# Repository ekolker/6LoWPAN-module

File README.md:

**[UNMAINTAINED] This library does not have a maintainer. The source code and repository will be kept at this URL indefinitely. If you'd like to help maintain this codebase, create an issue on this repo explaining why you'd like to become a maintainer and tag @tessel/maintainers in the body.**

6LoWPAN-module
==============

A [6LoWPAN](http://en.wikipedia.org/wiki/6LoWPAN) module for Tessel.

Designs in KiCad.

### License

Copyright 2014 Technical Machine, Inc.

CC-BY-SA

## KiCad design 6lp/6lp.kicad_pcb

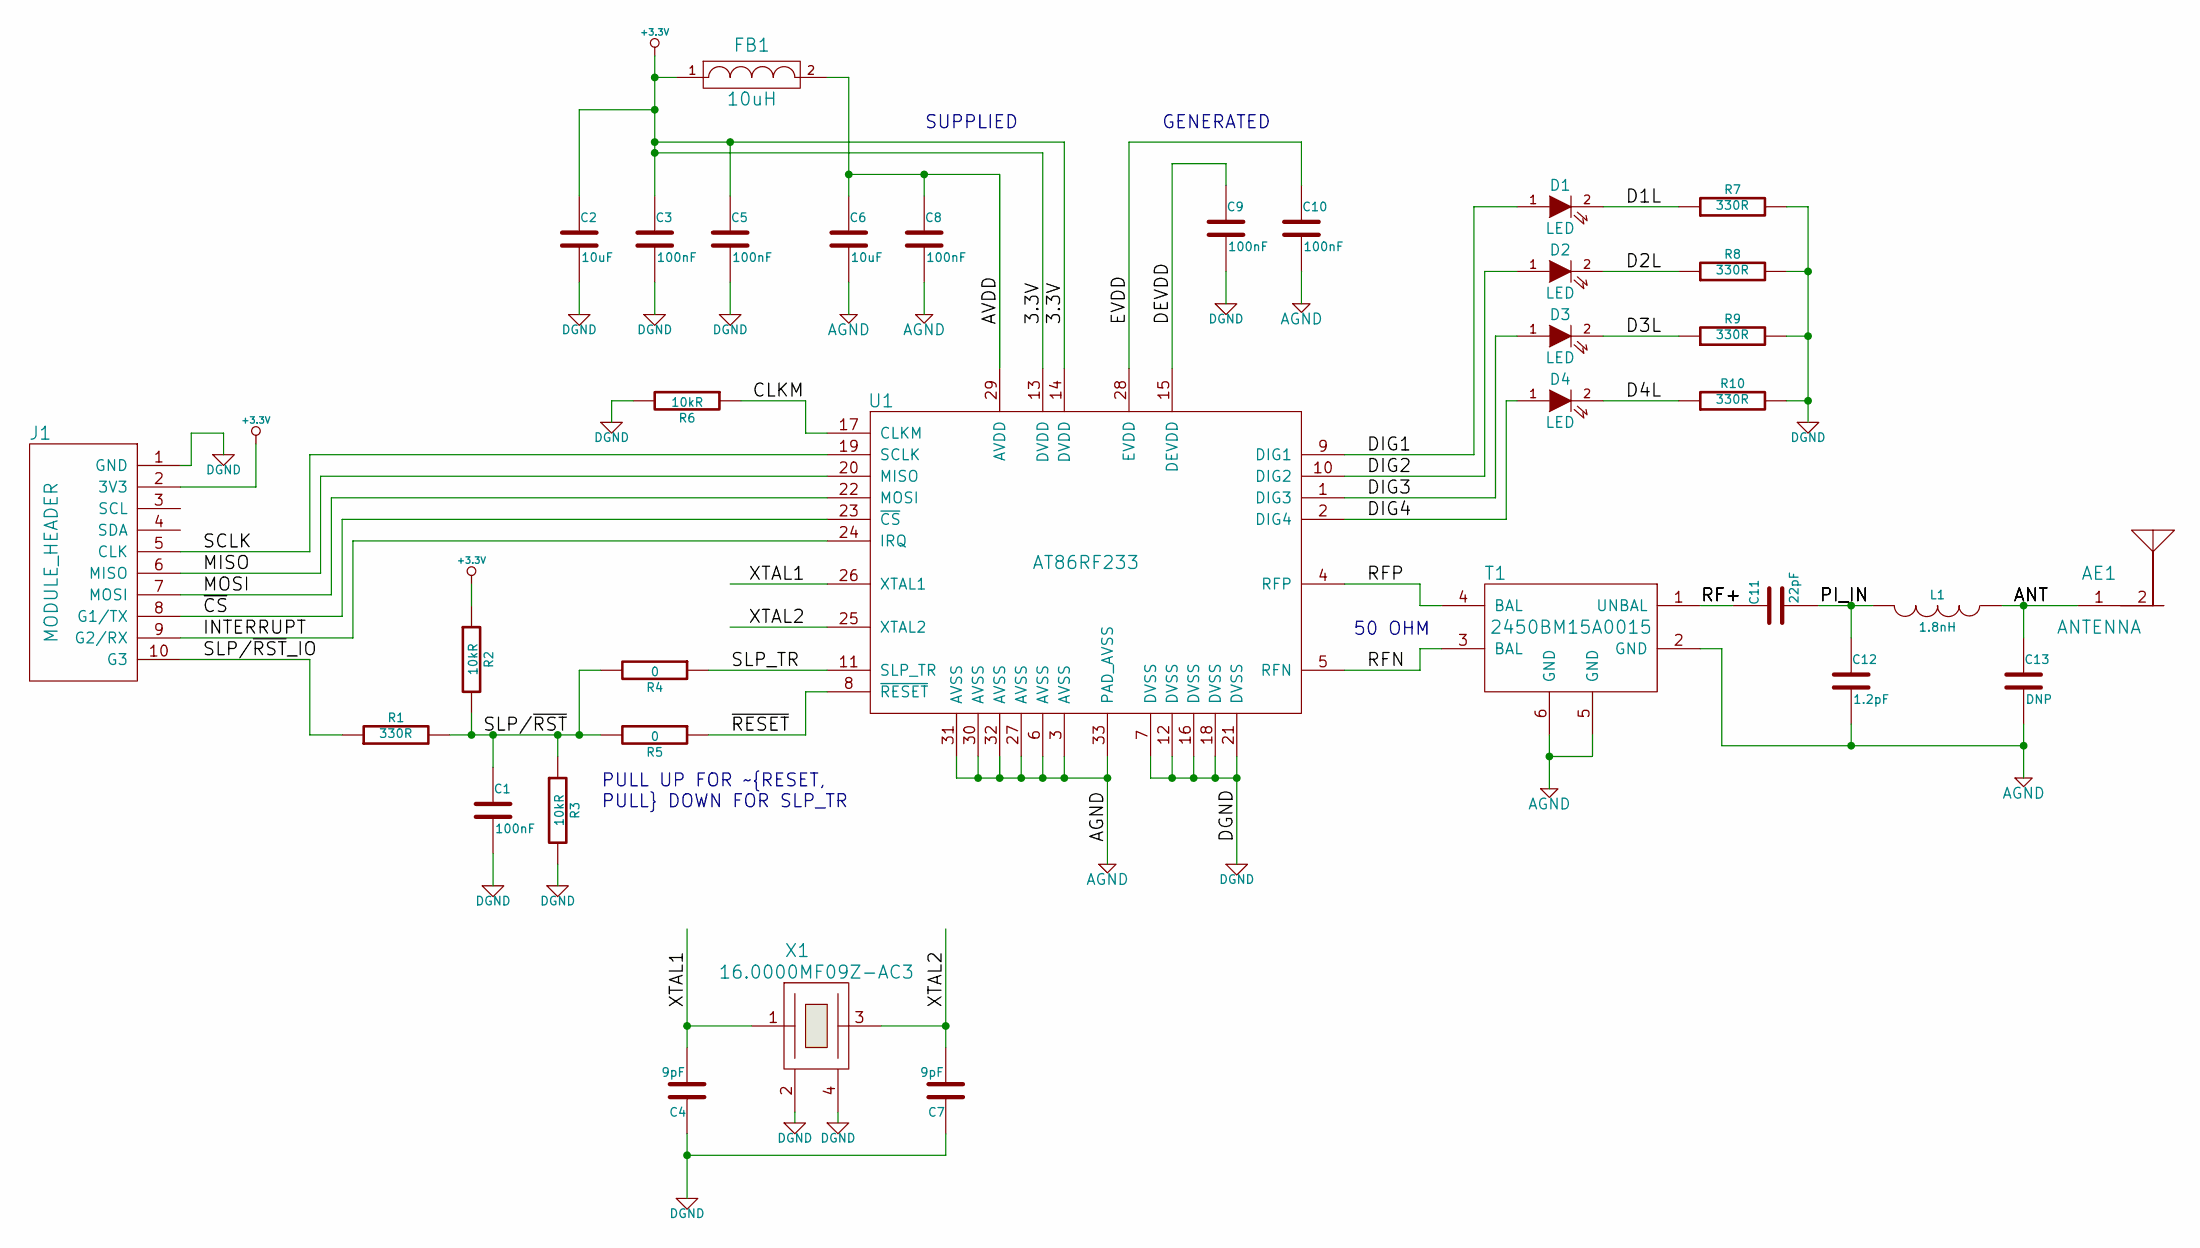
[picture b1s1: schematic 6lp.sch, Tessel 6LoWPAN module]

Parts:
AE1: ANTENNA; ANTENNA-SMT-2.45GHz
C1, C3, C5, C8, C9, C10: 100nF; C_0402
C2, C6: 10uF; C_0805
C4, C7: 9pF; C_0402
C11: 22pF; C_0402
C12: 1.2pF; C_0402
C13: DNP; C_0402
D1, D2, D3, D4: LED; LED-0603
FB1: 10uH; C_0603
J1: MODULE_HEADER; MODULE_HEADER_MODULE
L1: 1.8nH; C_0402
R1, R7, R8, R9, R10: 330R; R_0402
R2, R3, R6: 10kR; R_0402
R4, R5: 0; R_0402
T1: 2450BM15A0015
U1: AT86RF233; QFN-32-1EP
X1: 16.0000MF09Z-AC3; TSX-3225

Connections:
+3.3V: C2.1, C3.1, C5.1, FB1.1, J1.2 (3V3), R2.1, U1.13 (DVDD), U1.14 (DVDD)
/ANT: AE1.1, C13.1, L1.1
/AVDD: C6.1, C8.1, FB1.2, U1.29 (AVDD)
/CLKM: R6.1, U1.17 (CLKM)
/D1L: D1.2 (K), R7.1
/D2L: D2.2 (K), R8.1
/D3L: D3.2 (K), R9.1
/D4L: D4.2 (K), R10.1
/DEVDD: C9.1, U1.15 (DEVDD)
/DIG1: D1.1 (A), U1.9 (DIG1)
/DIG2: D2.1 (A), U1.10 (DIG2)
/DIG3: D3.1 (A), U1.1 (DIG3)
/DIG4: D4.1 (A), U1.2 (DIG4)
/EVDD: C10.1, U1.28 (EVDD)
/INTERRUPT: J1.9 (G2/RX), U1.24 (IRQ)
/MISO: J1.6 (MISO), U1.20 (MISO)
/MOSI: J1.7 (MOSI), U1.22 (MOSI)
/PI_IN: C11.2, C12.1, L1.2
/RF+: C11.1, T1.1 (UNBAL)
/RFN: T1.3 (BAL), U1.5 (RFN)
/RFP: T1.4 (BAL), U1.4 (RFP)
/SCLK: J1.5 (CLK), U1.19 (SCLK)
/SLP/~RST: C1.1, R1.2, R2.2, R3.1, R4.2, R5.2
/SLP/~RST~_IO: J1.10 (G3), R1.1
/SLP_TR: R4.1, U1.11 (SLP_TR)
/XTAL1: C4.2, U1.26 (XTAL1), X1.1
/XTAL2: C7.2, U1.25 (XTAL2), X1.3
/~CS: J1.8 (G1/TX), U1.23 (~CS)
/~RESET: R5.1, U1.8 (~RESET)
AGND: C6.2, C8.2, C10.2, C12.2, C13.2, T1.2 (GND), T1.5 (GND), T1.6 (GND), U1.3 (AVSS), U1.6 (AVSS), U1.27 (AVSS), U1.30 (AVSS), U1.31 (AVSS), U1.32 (AVSS), U1.33 (PAD_AVSS); also elsewhere on the board
DGND: C1.2, C2.2, C3.2, C4.1, C5.2, C7.1, C9.2, J1.1 (GND), R3.2, R6.2, R7.2, R8.2, R9.2, R10.2, U1.7 (DVSS), U1.12 (DVSS), U1.16 (DVSS), U1.18 (DVSS), U1.21 (DVSS), X1.2, X1.4; also elsewhere on the board

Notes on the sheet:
GENERATED
SUPPLIED
50 OHM
PULL UP FOR ~RESET, PULL DOWN FOR SLP_TR

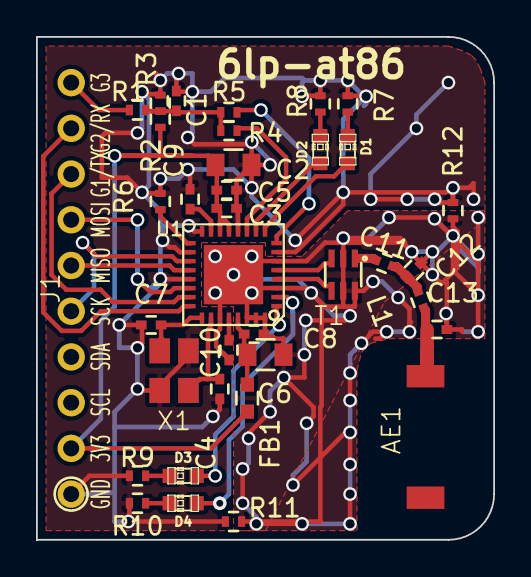
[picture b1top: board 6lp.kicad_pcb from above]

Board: 2 copper layers, 25.4 x 27.9 mm, 36 parts (0 on the bottom side), 31 nets.

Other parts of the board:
R11, R12: 0; R_0402

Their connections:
AGND: R11.2, R12.2; also elsewhere on the board
DGND: R11.1, R12.1; also elsewhere on the board

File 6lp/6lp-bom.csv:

"Id";"Designator";"Package";"Quantity";"Designation";"Supplier and ref";
1;"R5,R4,R11,R12";"Resistors_SMD:R_0402";4;"0";;;
2;"D1,D2,D3,D4";"LEDs:LED-0603";4;"LED";;;
3;"AE1";"parts:ANTENNA-SMT-2.45GHz";1;"ANTENNA";;;
4;"C11";"Capacitors_SMD:C_0402";1;"22pF";;;
5;"C12";"Capacitors_SMD:C_0402";1;"1.2pF";;;
6;"C13";"Capacitors_SMD:C_0402";1;"DNP";;;
7;"L1";"Capacitors_SMD:C_0402";1;"1.8nH";;;
8;"R7,R8,R9,R10,R1";"Resistors_SMD:R_0402";5;"330R";;;
9;"T1";"parts:EIA-0805";1;"2450BM15A0015";;;
10;"C1,C3,C5,C8,C9,C10";"Capacitors_SMD:C_0402";6;"100nF";;;
11;"C2,C6";"Capacitors_SMD:C_0805";2;"10uF";;;
12;"C4,C7";"Capacitors_SMD:C_0402";2;"9pF";;;
13;"FB1";"Capacitors_SMD:C_0603";1;"10uH";;;
14;"R2,R3,R6";"Resistors_SMD:R_0402";3;"10kR";;;
15;"U1";"SMD_Packages:QFN-32-1EP";1;"AT86RF233";;;
16;"X1";"parts:TSX-3225";1;"16.0000MF09Z-AC3";;;
17;"J1";"parts:MODULE_HEADER_MODULE";1;"MODULE_HEADER";;;

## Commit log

2014-10-15 swapped to AT86RF233
2014-10-15 at86rf233 sch complete, parts associated
2014-10-15 text, sch position tweaks
2014-10-15 pcb started w/ netlist
2014-10-15 board outline, header placement
2014-10-15 invisible values
2014-10-15 placement round one...
2014-10-15 closed project for review
2014-10-15 gerbers
2014-10-15 pdf schematic
2014-10-15 drill file may not have gone through properly last time?
2014-10-15 sent to manufacturer as-is
2014-10-15 gerber zip
2014-10-16 bom and rando xml file
2014-10-16 forgot back mask...
2014-10-16 for real the ones we sent for manufacture
2014-10-17 i really want to like you, apc, but sometimes...
2014-10-17 moved a via i guess
2014-10-20 damn you, apc
2014-10-24 pdf export because jia is unfathomably lazy and has not yet gotten kicad working. let me remind you that i switched computers (physical machines) as well as my OS to do so...
2016-08-23 Adds unmaintained notice
